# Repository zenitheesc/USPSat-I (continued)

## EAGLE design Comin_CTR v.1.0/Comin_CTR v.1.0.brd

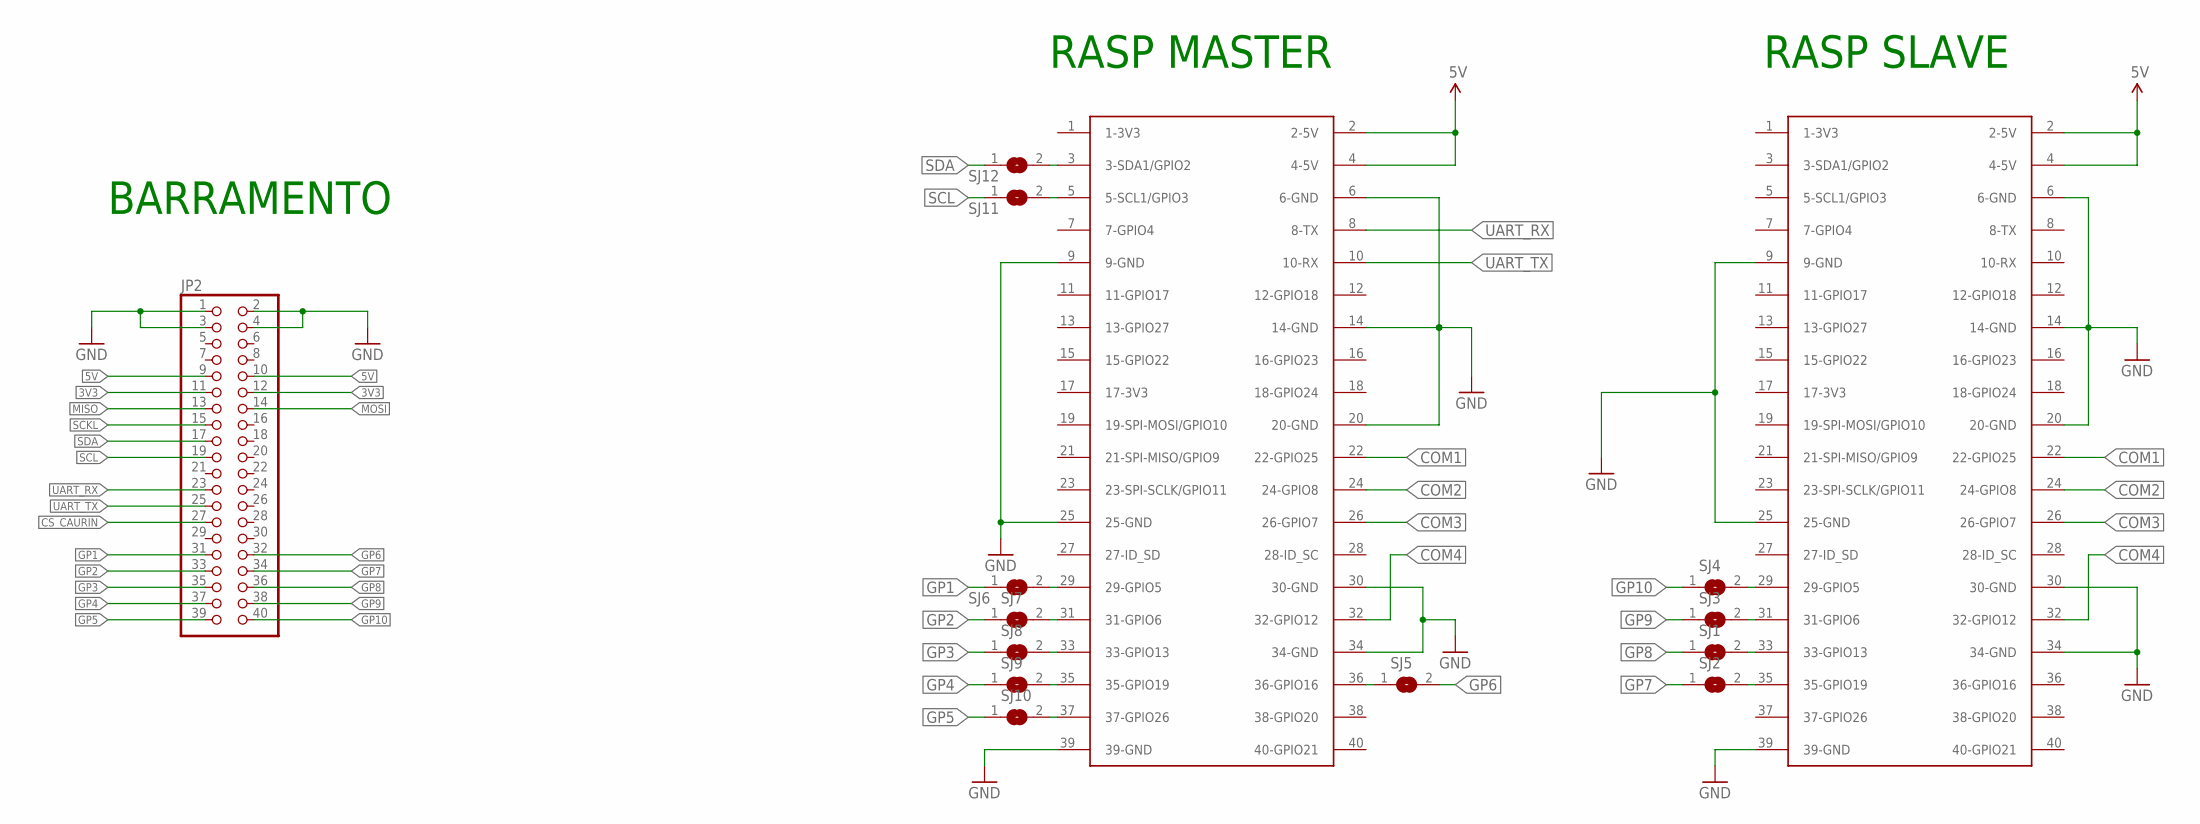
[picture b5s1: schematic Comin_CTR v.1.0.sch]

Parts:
JP2: PINHD-2X20; 2X20
SJ1, SJ2, SJ3, SJ4, SJ5, SJ6, SJ7, SJ8, SJ9, SJ10, SJ11, SJ12: SJ
U$1, U$2: RASPBERRY-PI+PIZERO; RASPBERRY-PI-ZERO

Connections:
3V3: JP2.11, JP2.12
5V: JP2.9, JP2.10, U$1.2 (2-5V), U$1.4 (4-5V), U$2.2 (2-5V), U$2.4 (4-5V)
COM1: U$1.22 (22-GPIO25), U$2.22 (22-GPIO25)
COM2: U$1.24 (24-GPIO8), U$2.24 (24-GPIO8)
COM3: U$1.26 (26-GPIO7), U$2.26 (26-GPIO7)
COM4: U$1.32 (32-GPIO12), U$2.32 (32-GPIO12)
CS_CAURIN: JP2.27
GND: JP2.1, JP2.2, JP2.3, JP2.4, U$1.6 (6-GND), U$1.9 (9-GND), U$1.14 (14-GND), U$1.20 (20-GND), U$1.25 (25-GND), U$1.30 (30-GND), U$1.34 (34-GND), U$1.39 (39-GND), U$2.6 (6-GND), U$2.9 (9-GND), U$2.14 (14-GND), U$2.20 (20-GND), U$2.25 (25-GND), U$2.30 (30-GND), U$2.34 (34-GND), U$2.39 (39-GND)
GP1: JP2.31, SJ6.1
GP2: JP2.33, SJ7.1
GP3: JP2.35, SJ8.1
GP4: JP2.37, SJ9.1
GP5: JP2.39, SJ10.1
GP6: JP2.32, SJ5.2
GP7: JP2.34, SJ2.1
GP8: JP2.36, SJ1.1
GP9: JP2.38, SJ3.1
GP10: JP2.40, SJ4.1
MISO: JP2.13
MOSI: JP2.14
unnamed: SJ1.2, U$1.33 (33-GPIO13)
unnamed: SJ2.2, U$1.35 (35-GPIO19)
unnamed: SJ3.2, U$1.31 (31-GPIO6)
unnamed: SJ5.1, U$2.36 (36-GPIO16)
unnamed: SJ4.2, U$1.29 (29-GPIO5)
unnamed: SJ6.2, U$2.29 (29-GPIO5)
unnamed: SJ7.2, U$2.31 (31-GPIO6)
unnamed: SJ8.2, U$2.33 (33-GPIO13)
unnamed: SJ9.2, U$2.35 (35-GPIO19)
unnamed: SJ10.2, U$2.37 (37-GPIO26)
unnamed: SJ11.2, U$2.5 (5-SCL1/GPIO3)
unnamed: SJ12.2, U$2.3 (3-SDA1/GPIO2)
SCKL: JP2.15
SCL: JP2.19, SJ11.1
SDA: JP2.17, SJ12.1
UART_RX: JP2.23, U$2.8 (8-TX)
UART_TX: JP2.25, U$2.10 (10-RX)

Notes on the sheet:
RASP MASTER
RASP SLAVE
BARRAMENTO

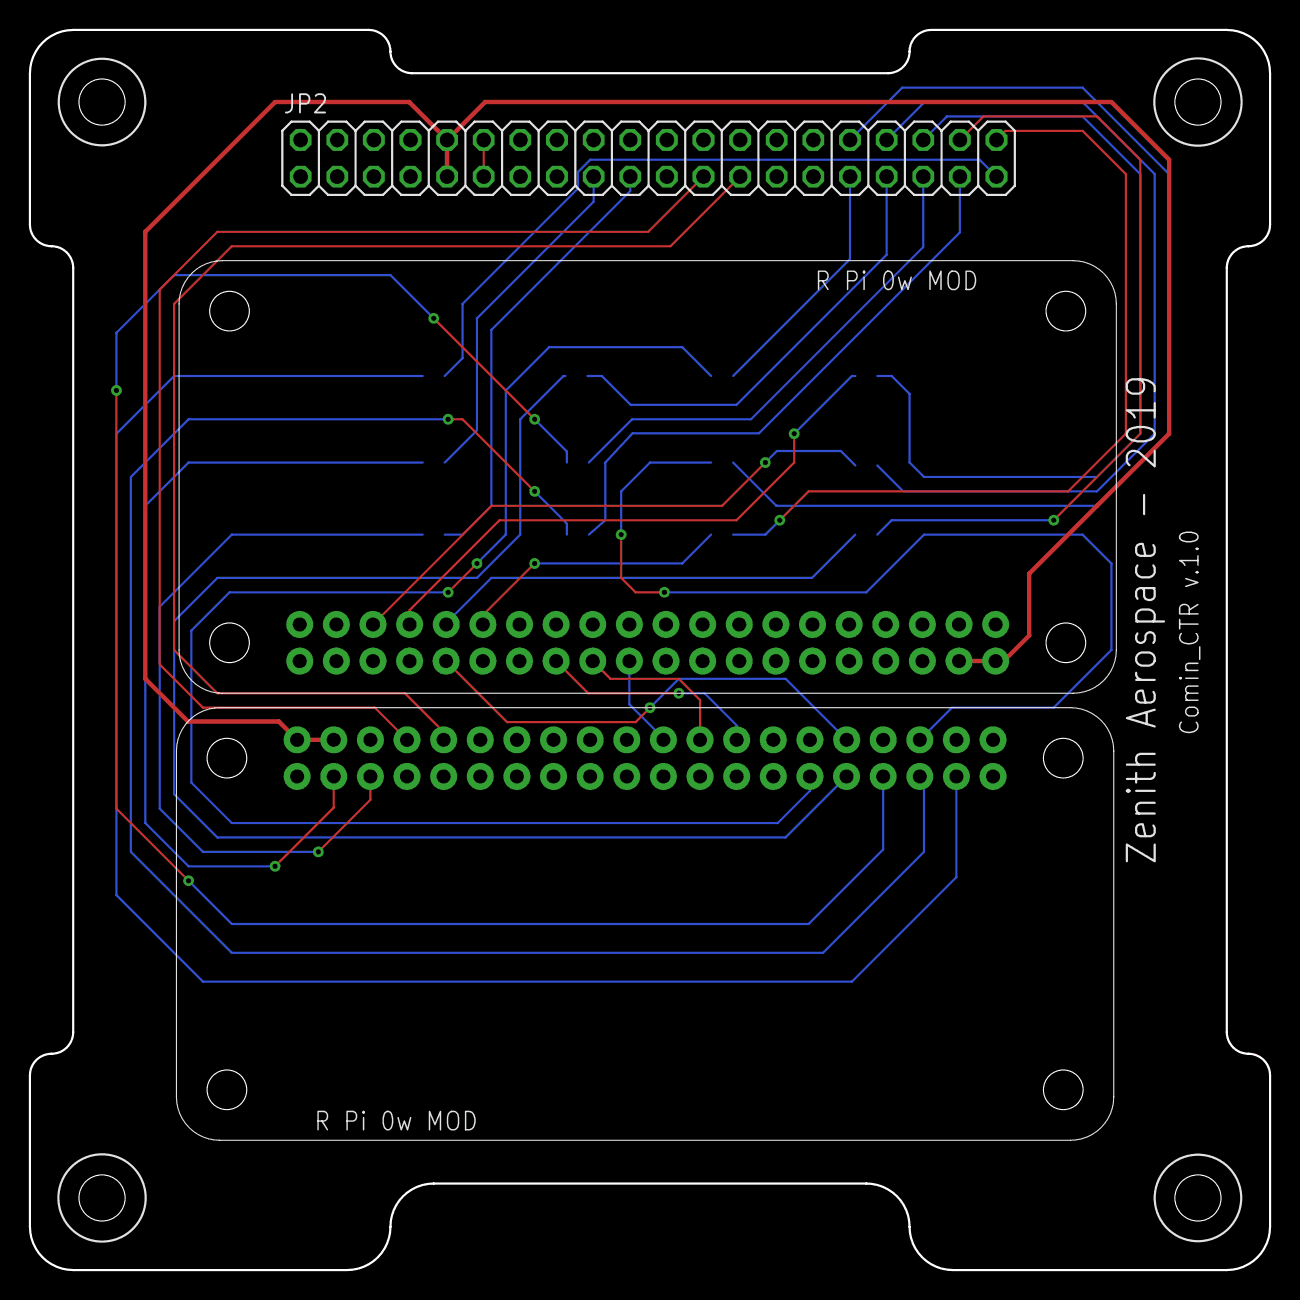
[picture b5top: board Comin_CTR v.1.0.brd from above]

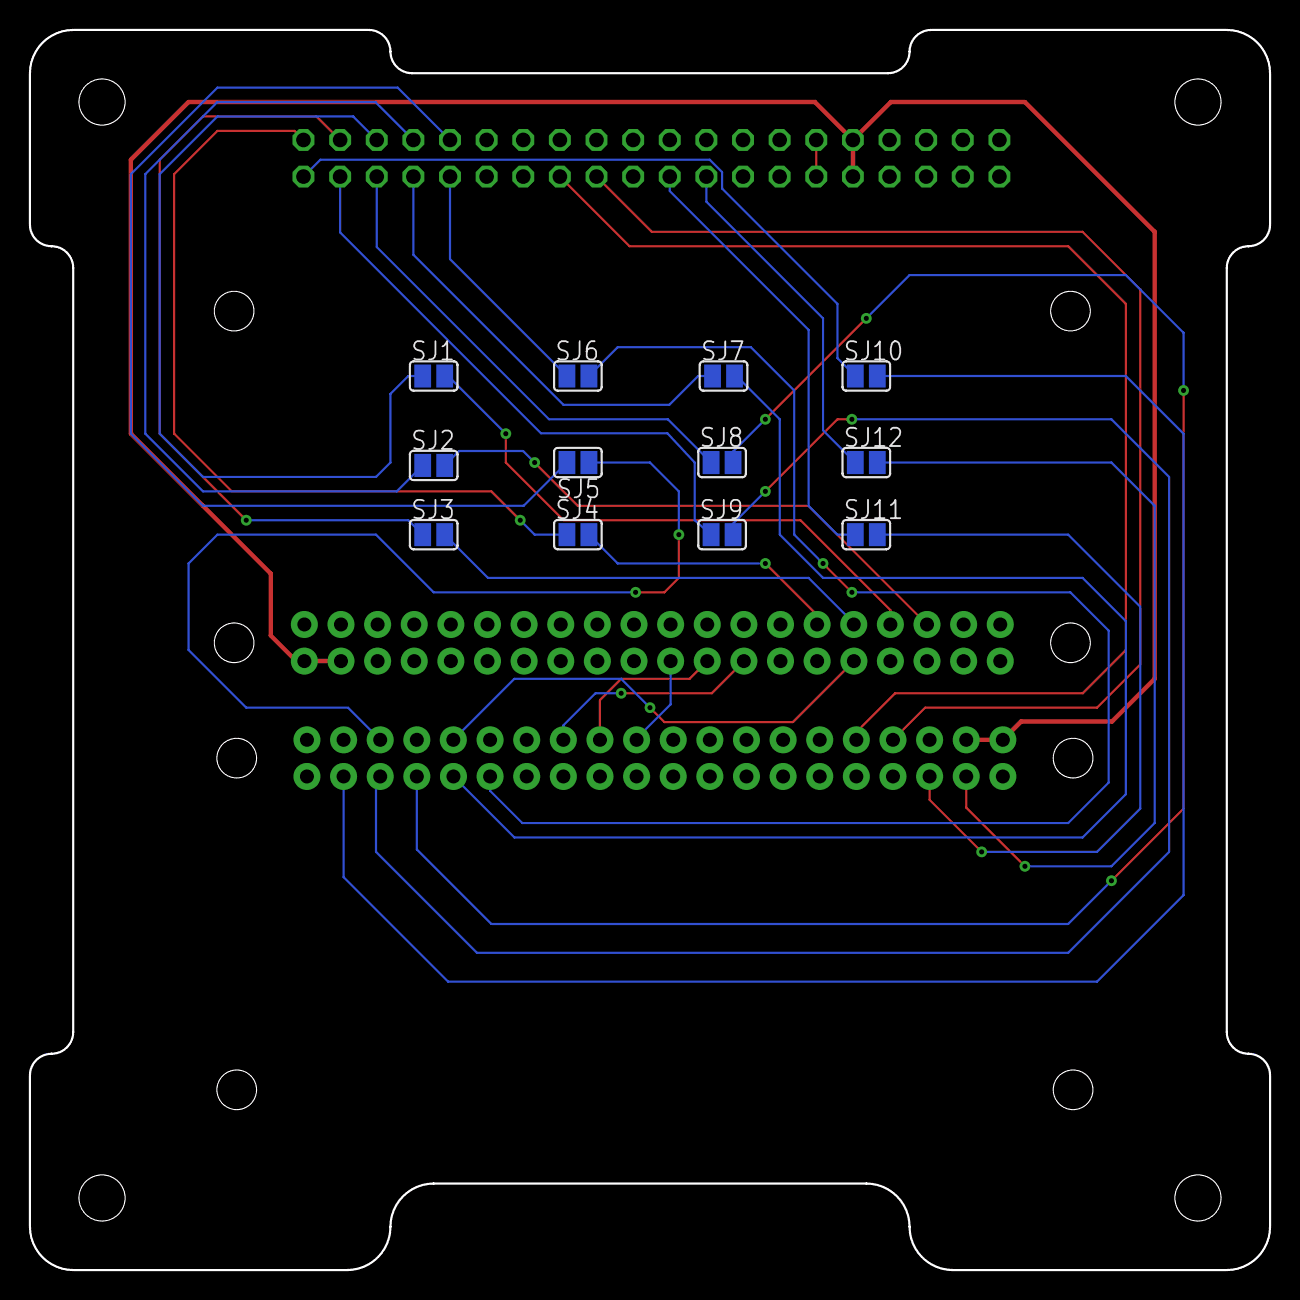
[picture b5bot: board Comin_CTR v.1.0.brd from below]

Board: 2 copper layers, 86.0 x 86.0 mm, 15 parts (12 on the bottom side), 33 nets.

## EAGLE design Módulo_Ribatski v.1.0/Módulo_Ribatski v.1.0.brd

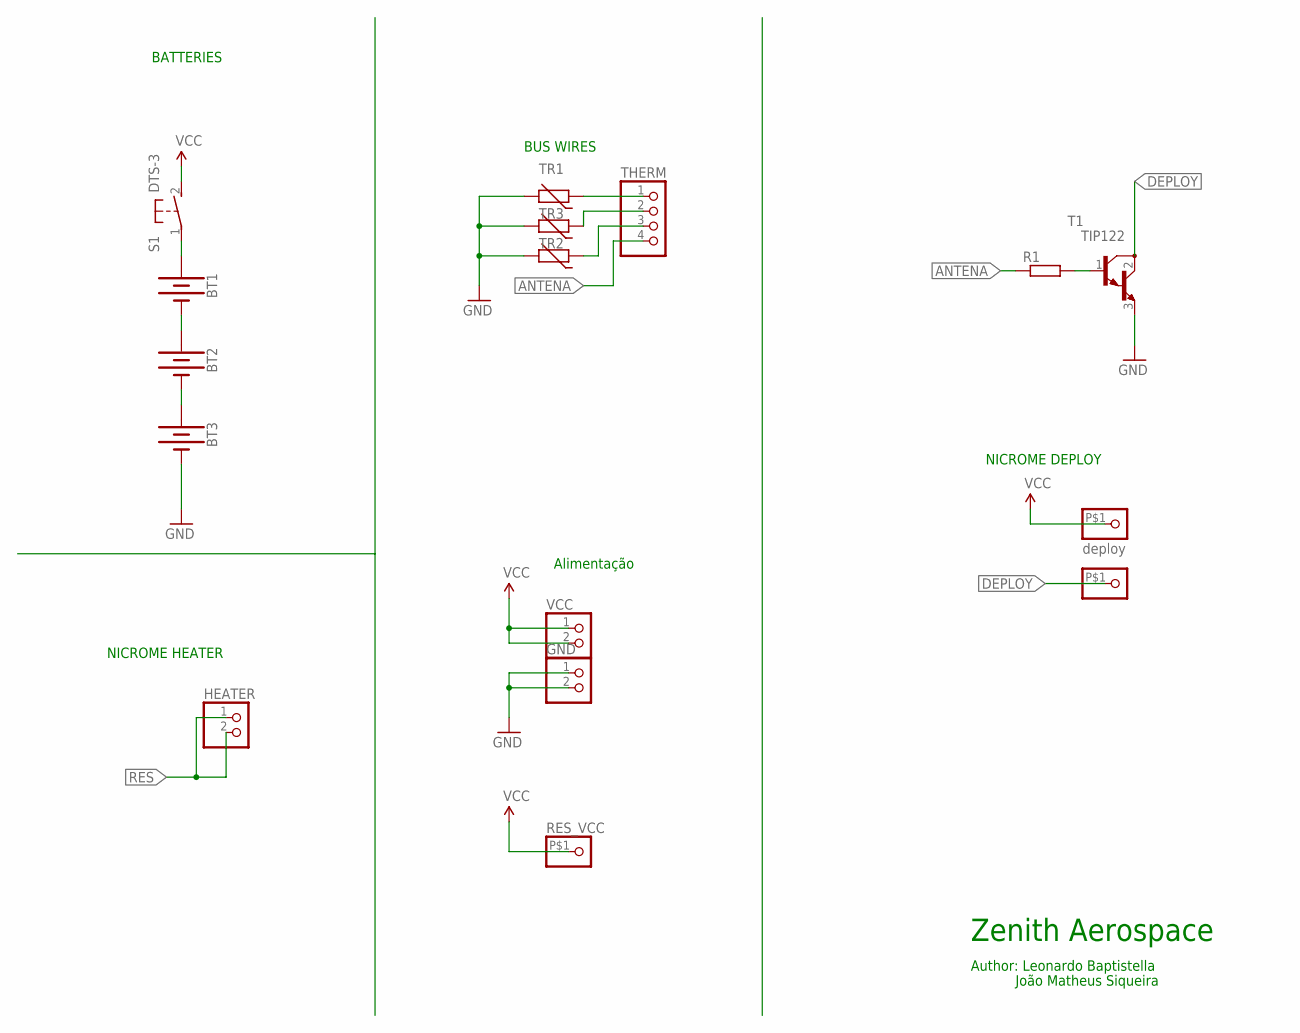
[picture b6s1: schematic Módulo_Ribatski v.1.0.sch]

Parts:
BT1, BT2, BT3: BATTERY-18650; BATTERY_18650-HOLDER
DEPLOY_GND: PINHD-1X1-BIGPOGO; 1X1-BIGPOGO
DEPLOY_VCC: deploy; 1X1-BIGPOGO
GND: PINHD-1X2; 1X02
HEATER: PINHD-1X2; 1X02
R1: R-EU_R1206; R1206
RES_VCC: PINHD-1X1-BIGPOGO; 1X1-BIGPOGO
S1: DTS-3
T1: TIP122; TO220
THERM: HEADER-1X4; 1X04_OVAL
TR1, TR2, TR3: THERMISTOR_R-5; R-5
VCC: PINHD-1X2; 1X02

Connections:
ANTENA: R1.1, THERM.4
DEPLOY: DEPLOY_GND.P$1, T1.2 (C)
GND: BT3.GND@1 (-), GND.1, GND.2, T1.3 (E), TR1.2, TR2.2, TR3.2
unnamed: BT1.GND@1 (-), BT2.PWR@1 (+)
unnamed: BT2.GND@1 (-), BT3.PWR@1 (+)
unnamed: THERM.1, TR1.1
unnamed: THERM.2, TR3.1
unnamed: THERM.3, TR2.1
unnamed: R1.2, T1.1 (B)
unnamed: BT1.PWR@1 (+), S1.1
RES: HEATER.1, HEATER.2
VCC: DEPLOY_VCC.P$1, RES_VCC.P$1, S1.2, VCC.1, VCC.2

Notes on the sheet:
NICROME HEATER
BUS WIRES
BATTERIES
Zenith Aerospace
Author: Leonardo Baptistella
João Matheus Siqueira
Alimentação
NICROME DEPLOY

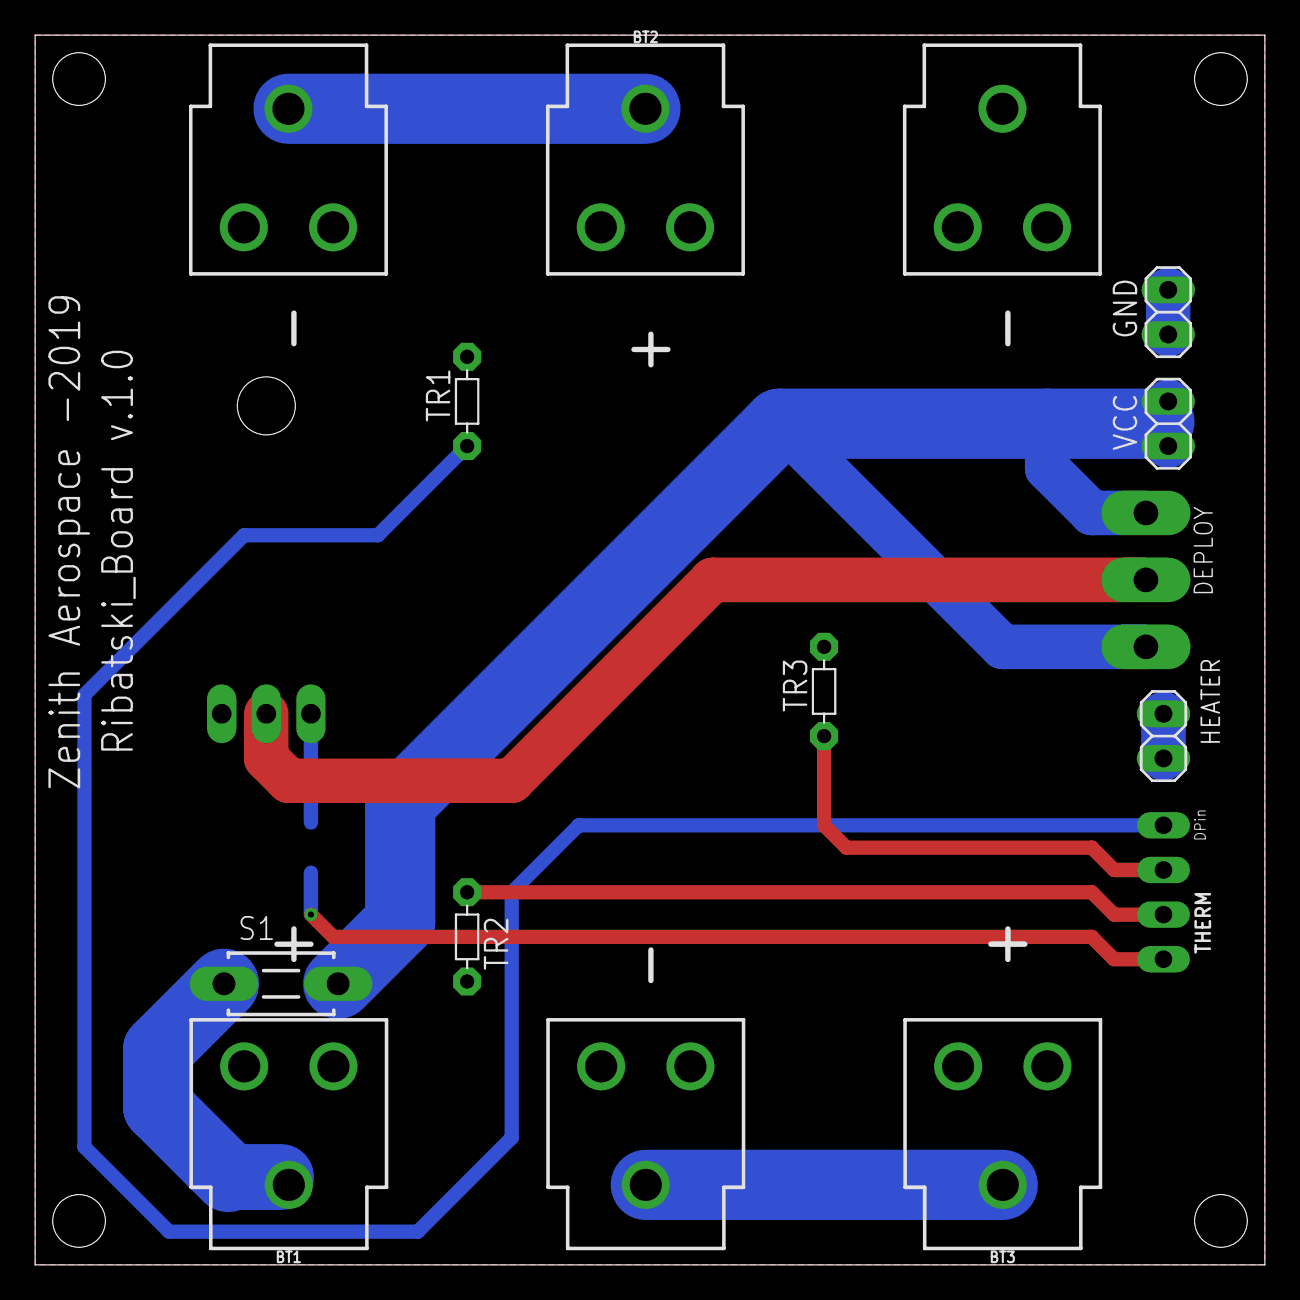
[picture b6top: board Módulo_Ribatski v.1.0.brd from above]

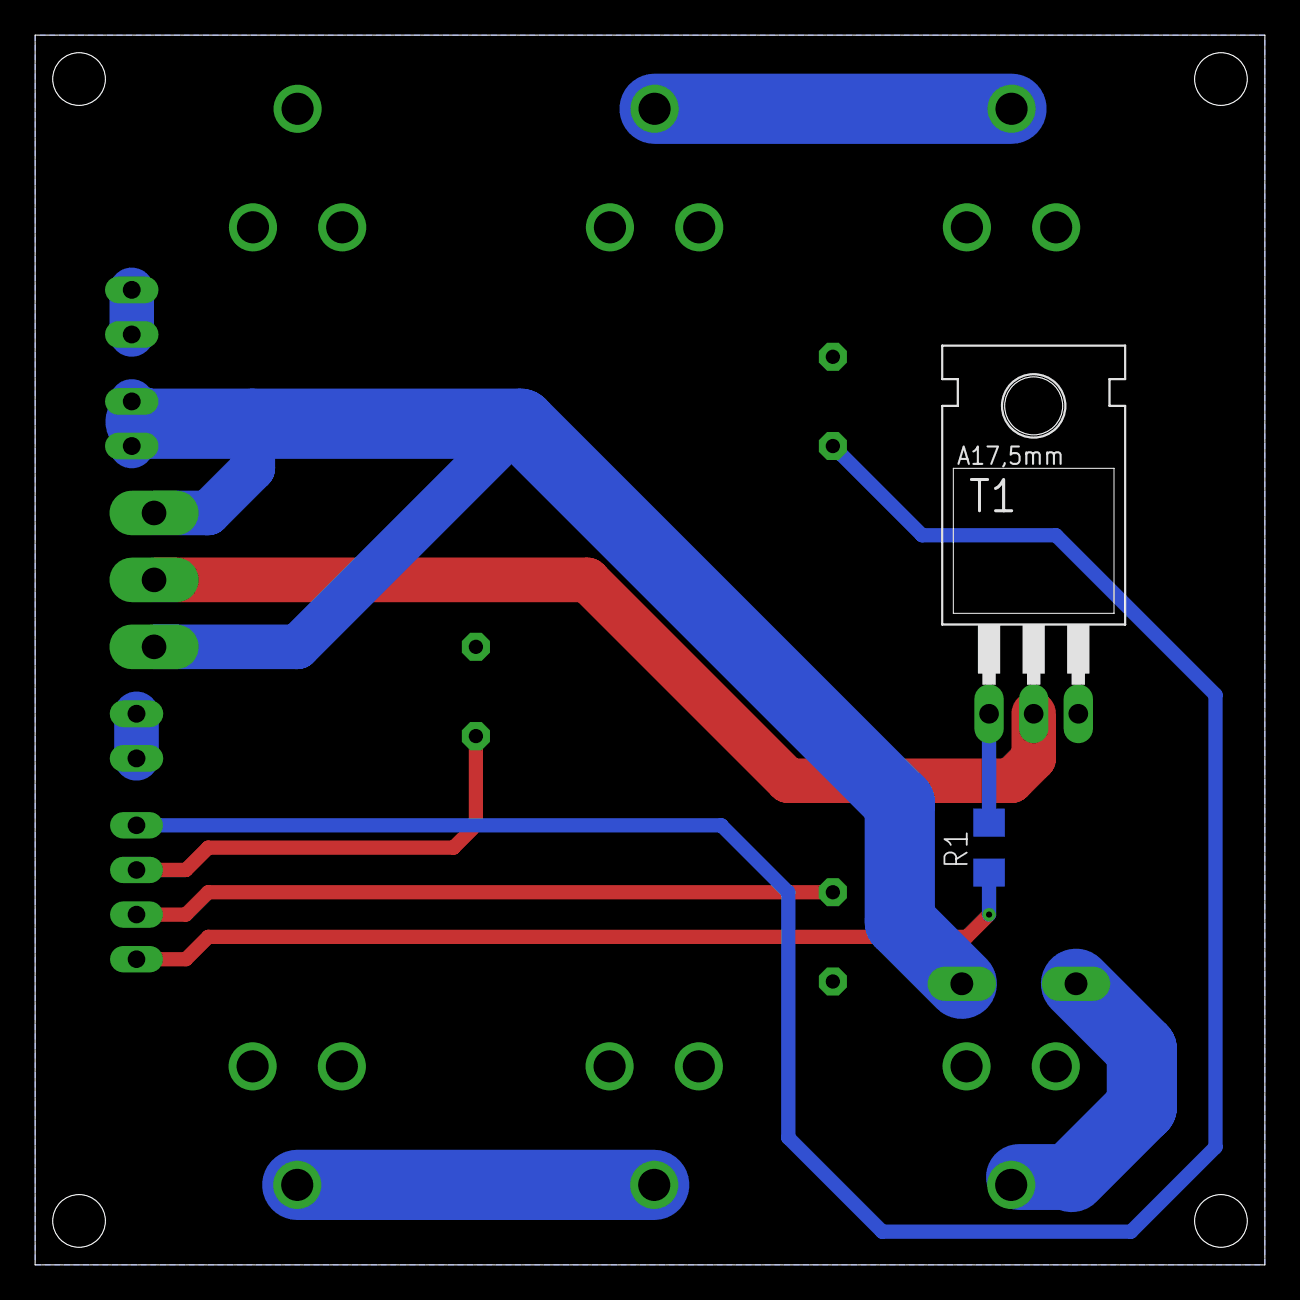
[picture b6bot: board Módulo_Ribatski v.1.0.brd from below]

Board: 2 copper layers, 70.0 x 70.0 mm, 16 parts (2 on the bottom side), 12 nets.

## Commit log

2020-06-10 first
2020-06-11 Added README.md with WIKI link
2020-06-11 documentation
2021-03-01 💬 - File Rebuilt | Github Action Runner : 1
2021-03-29 Name update
2021-03-29 Add Estruturras
2021-04-17 Update README.md
    minor changes
